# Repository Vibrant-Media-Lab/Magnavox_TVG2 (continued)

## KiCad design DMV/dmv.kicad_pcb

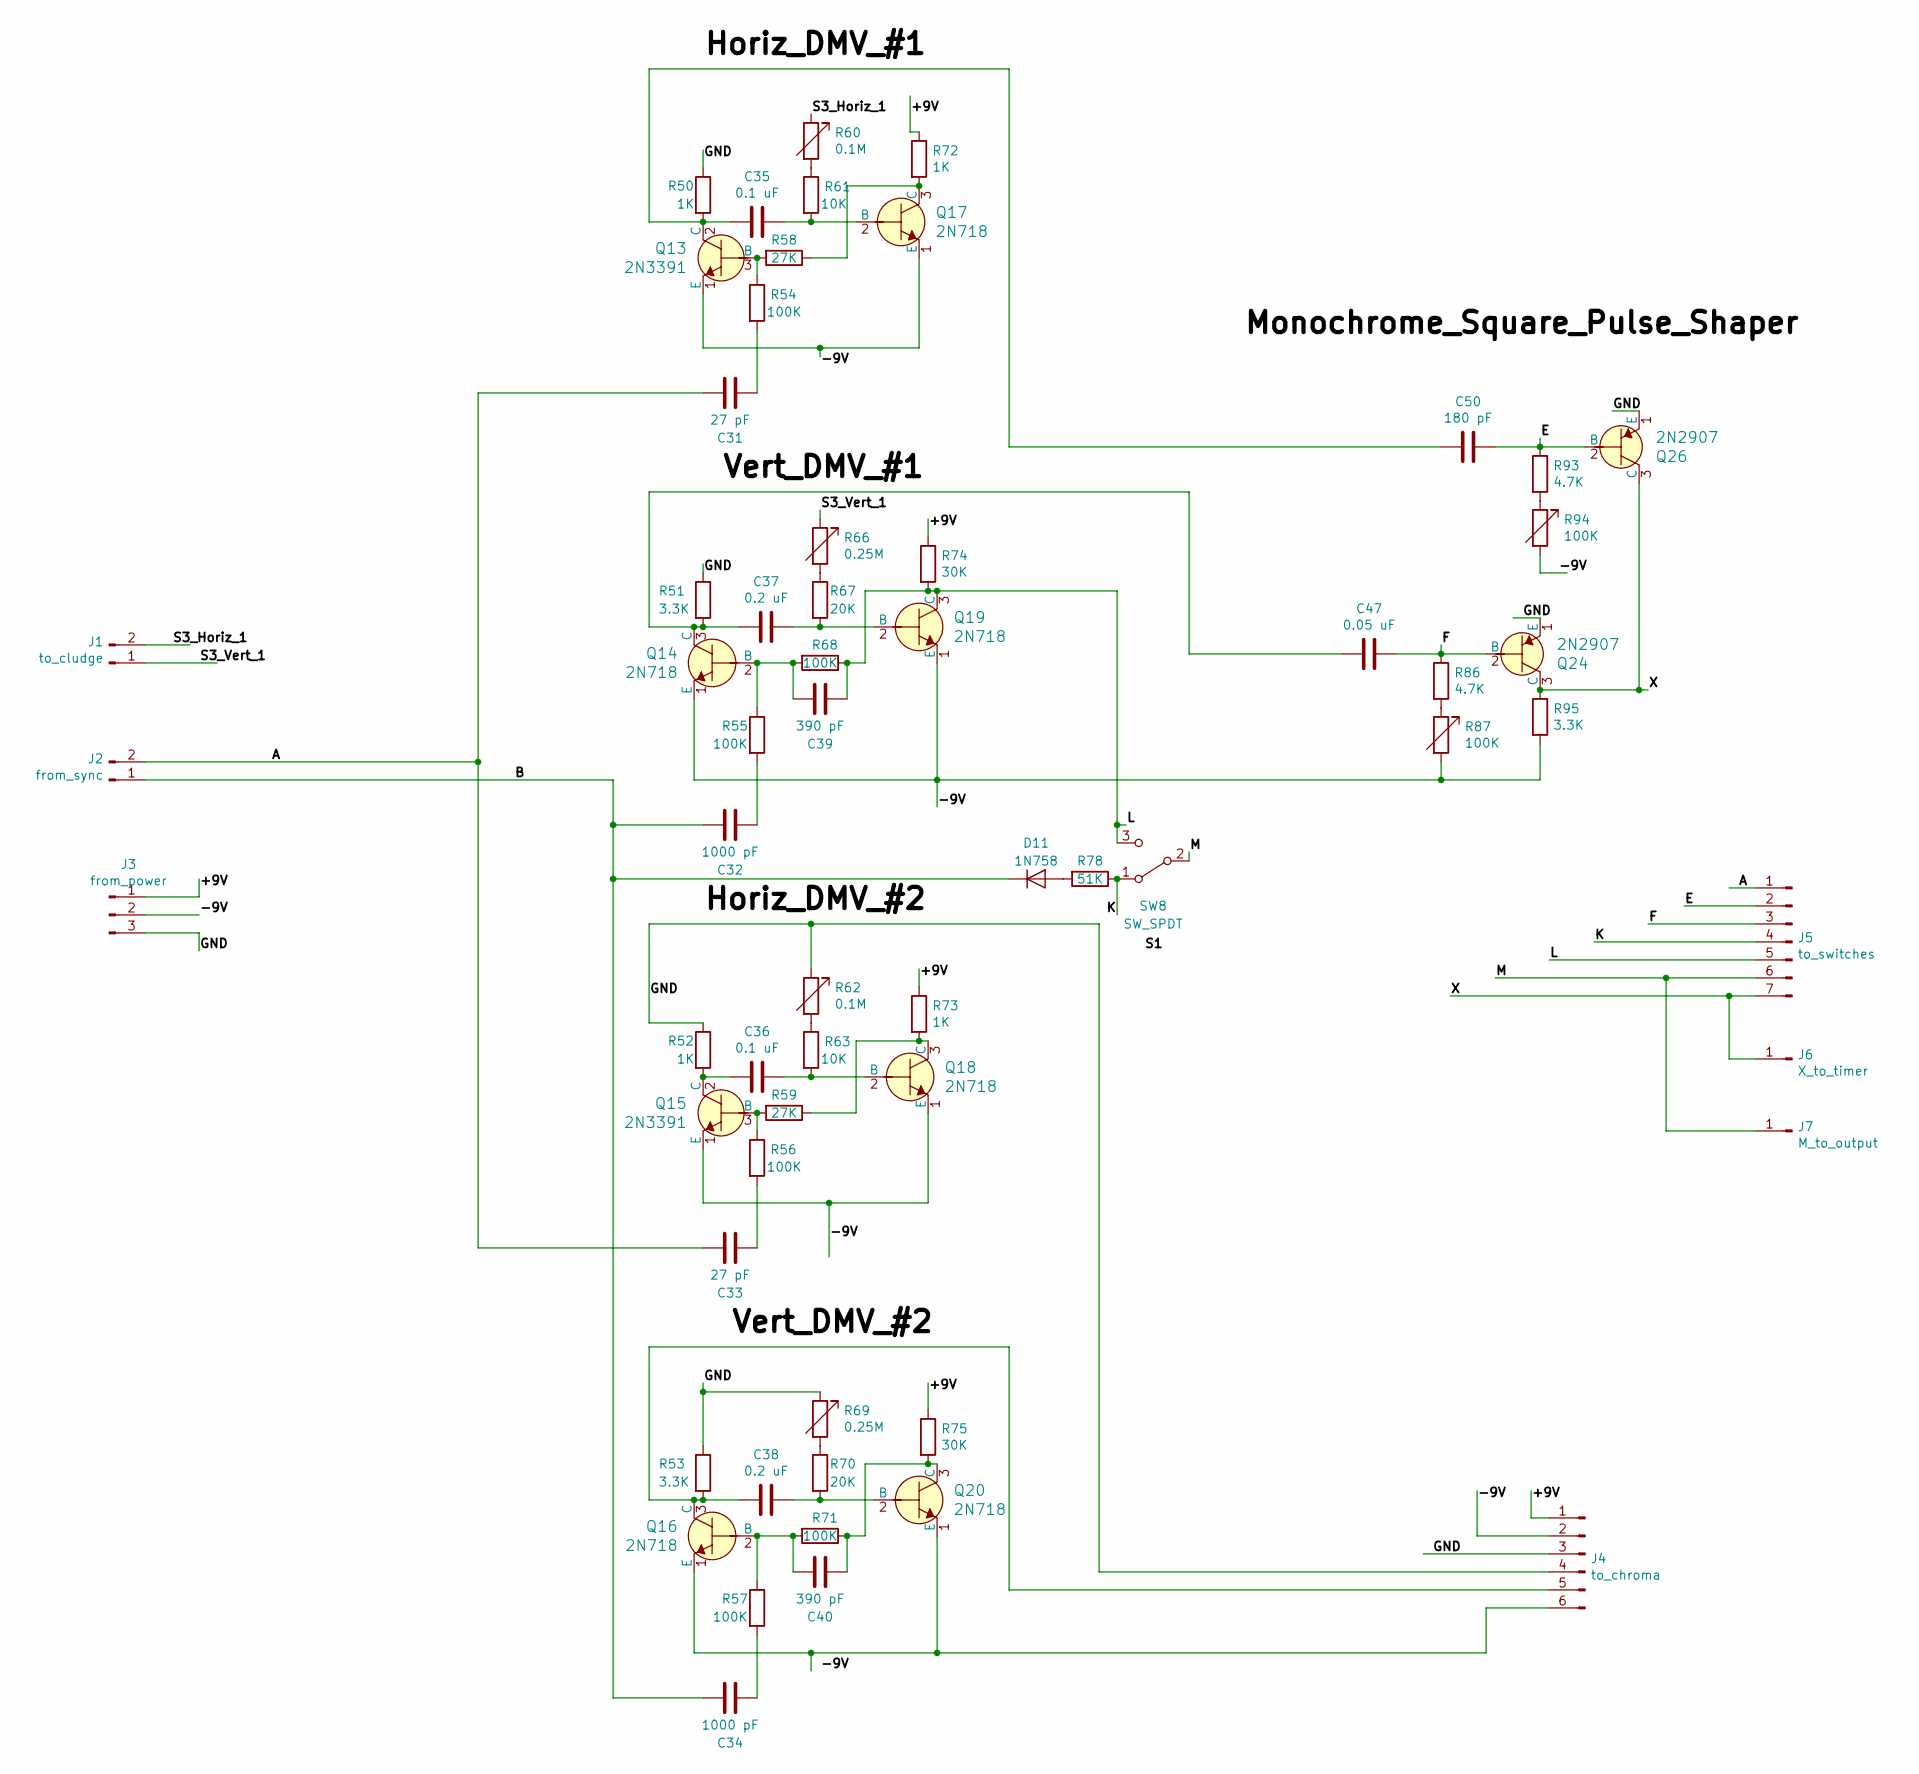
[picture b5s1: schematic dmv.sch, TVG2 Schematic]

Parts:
C31, C33: 27 pF; C_Disc_D4.7mm_W2.5mm_P5.00mm
C32, C34: 1000 pF; C_Disc_D4.7mm_W2.5mm_P5.00mm
C35, C36: 0.1 uF; C_Disc_D4.7mm_W2.5mm_P5.00mm
C37, C38: 0.2 uF; C_Disc_D4.7mm_W2.5mm_P5.00mm
C39, C40: 390 pF; C_Disc_D4.7mm_W2.5mm_P5.00mm
C47: 0.05 uF; C_Disc_D4.7mm_W2.5mm_P5.00mm
C50: 180 pF; C_Disc_D4.7mm_W2.5mm_P5.00mm
D11: 1N758; D_DO-41_SOD81_P10.16mm_Horizontal
J1: to_cludge; PinHeader_1x02_P2.54mm_Vertical
J2: from_sync; PinHeader_1x02_P2.54mm_Vertical
J3: from_power; PinHeader_1x03_P2.54mm_Vertical
J4: to_chroma; PinHeader_1x06_P2.54mm_Vertical
J5: to_switches; PinHeader_1x07_P2.54mm_Vertical
J6: X_to_timer; PinHeader_1x01_P2.54mm_Vertical
J7: M_to_output; PinHeader_1x01_P2.54mm_Vertical
Q13, Q15: 2N3391; TO-92-3; MPN 2N3904; Digi-Key_PN 2N3904CS-ND
Q14, Q16, Q17, Q18, Q19, Q20: 2N718; TO-92-3; MPN 2N5109; Digi-Key_PN 2N5109CS-ND
Q24, Q26: 2N2907; TO-92-3; MPN 2N2907A; Digi-Key_PN 2N2907ACS-ND
R50, R52, R72, R73: 1K; R_Axial_DIN0207_L6.3mm_D2.5mm_P7.62mm_Horizontal
R51, R53, R95: 3.3K; R_Axial_DIN0207_L6.3mm_D2.5mm_P7.62mm_Horizontal
R54, R55, R56, R57, R68, R71: 100K; R_Axial_DIN0207_L6.3mm_D2.5mm_P7.62mm_Horizontal
R58, R59: 27K; R_Axial_DIN0207_L6.3mm_D2.5mm_P7.62mm_Horizontal
R60, R62: 0.1M; Potentiometer_Bourns_3386F_Vertical
R61, R63: 10K; R_Axial_DIN0207_L6.3mm_D2.5mm_P7.62mm_Horizontal
R66, R69: 0.25M; Potentiometer_Bourns_3386F_Vertical
R67, R70: 20K; R_Axial_DIN0207_L6.3mm_D2.5mm_P7.62mm_Horizontal
R74, R75: 30K; R_Axial_DIN0207_L6.3mm_D2.5mm_P7.62mm_Horizontal
R78: 51K; R_Axial_DIN0207_L6.3mm_D2.5mm_P7.62mm_Horizontal
R86, R93: 4.7K; R_Axial_DIN0207_L6.3mm_D2.5mm_P7.62mm_Horizontal
R87, R94: 100K; Potentiometer_Bourns_3386F_Vertical
SW8: SW_SPDT; Toggle_Switch_100SP1T1B4M2QE

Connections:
/+9V: J3.1, J4.1, R72.1, R73.1, R74.1, R75.1
/-9V: J3.2, J4.2, Q14.1 (E), Q15.1 (E), Q18.1 (E), Q19.1 (E), R87.2, R94.2, R95.2
/A: C31.1, C33.1, J2.2, J5.1
/B: C32.2, C34.2, D11.1 (K), J2.1
/E: C50.1, J5.2, Q26.2 (B), R93.1
/F: C47.1, J5.3, Q24.2 (B), R86.1
/GND: J3.3, J4.3, J4.4, Q24.1 (E), Q26.1 (E), R50.1, R51.1, R52.1, R53.1, R62.1, R69.1
/K: J5.4, R78.1, SW8.1 (A)
/L: C39.1, J5.5, Q19.3 (C), R68.1, R74.2, SW8.3 (C)
/M: J5.6, J7.1, SW8.2 (B)
/S3_Horiz_1: J1.2, R60.1
/S3_Vert_1: J1.1, R66.1
/X: J5.7, J6.1, Q24.3 (C), Q26.3 (C), R95.1
unnamed: C31.2, R54.2
unnamed: C32.1, R55.2
unnamed: C33.2, R56.2
unnamed: C34.1, R57.2
unnamed: C35.1, C50.2, Q13.2 (C), R50.2
unnamed: C35.2, Q17.2 (B), R61.2
unnamed: C36.1, Q15.2 (C), R52.2
unnamed: C36.2, Q18.2 (B), R63.2
unnamed: C37.1, Q19.2 (B), R67.2
unnamed: C37.2, C47.2, Q14.3 (C), R51.2
unnamed: C38.1, Q20.2 (B), R70.2
unnamed: C38.2, J4.5, Q16.3 (C), R53.2
unnamed: C39.2, Q14.2 (B), R55.1, R68.2
unnamed: C40.1, Q20.3 (C), R71.1, R75.2
unnamed: C40.2, Q16.2 (B), R57.1, R71.2
unnamed: D11.2 (A), R78.2
unnamed: J4.6, Q16.1 (E), Q20.1 (E)
unnamed: Q13.1 (E), Q17.1 (E)
unnamed: Q13.3 (B), R54.1, R58.2
unnamed: Q15.3 (B), R56.1, R59.2
unnamed: Q17.3 (C), R58.1, R72.2
unnamed: Q18.3 (C), R59.1, R73.2
unnamed: R60.2, R61.1
unnamed: R62.2, R63.1
unnamed: R66.2, R67.1
unnamed: R69.2, R70.1
unnamed: R86.2, R87.1
unnamed: R93.2, R94.1

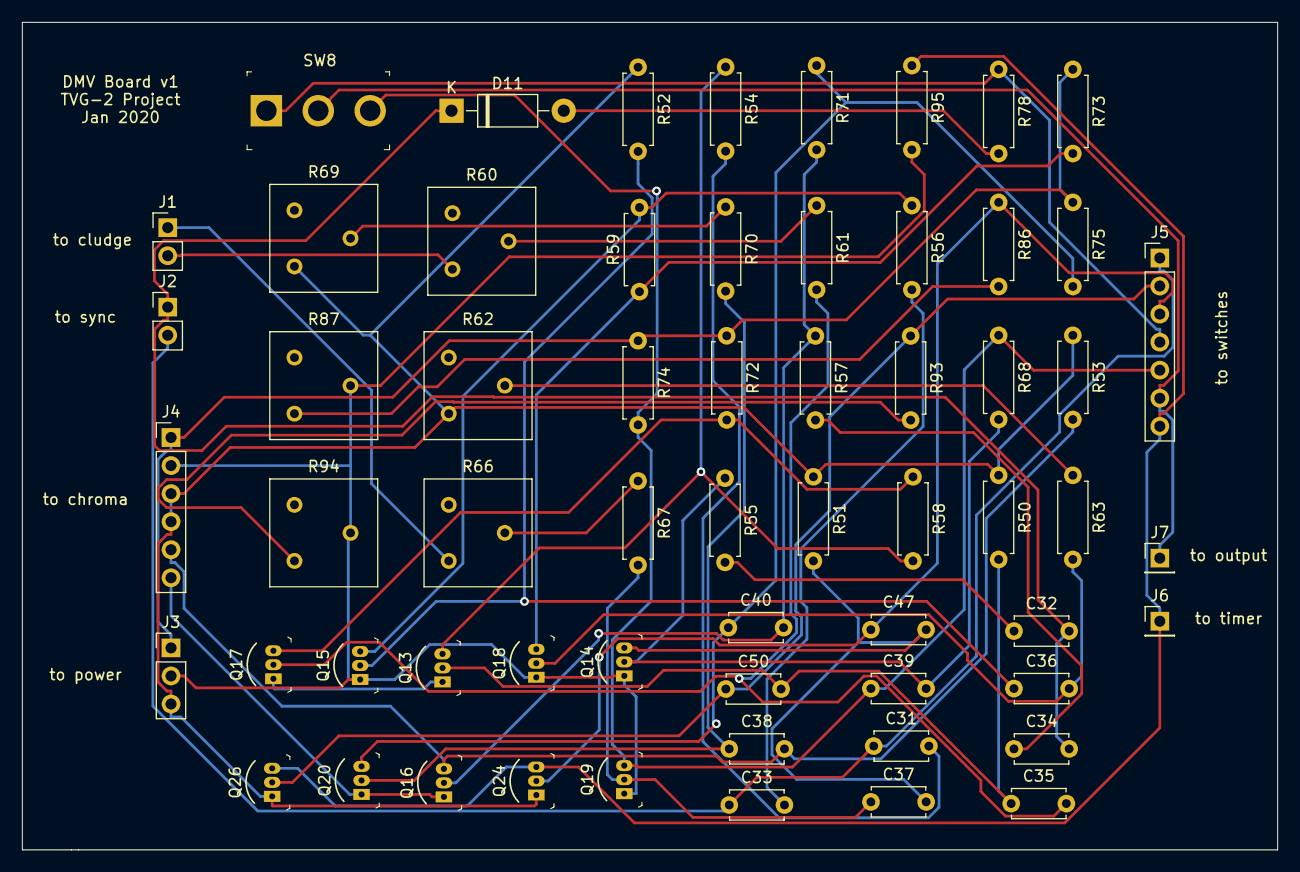
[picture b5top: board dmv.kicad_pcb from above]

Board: 2 copper layers, 113.7 x 74.9 mm, 61 parts (0 on the bottom side), 41 nets.

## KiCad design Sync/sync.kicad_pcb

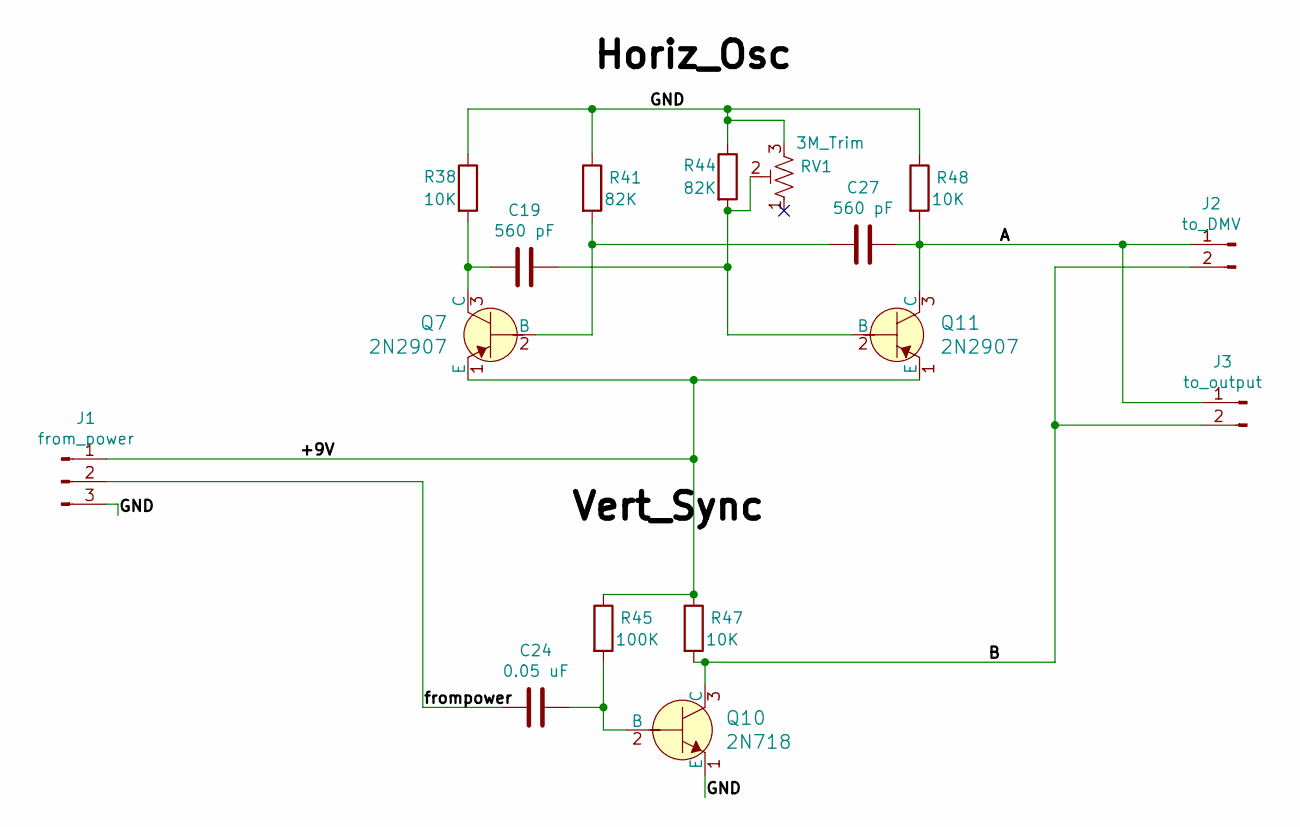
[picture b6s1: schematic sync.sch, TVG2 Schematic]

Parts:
C19, C27: 560 pF; C_Disc_D4.7mm_W2.5mm_P5.00mm
C24: 0.05 uF; C_Disc_D4.7mm_W2.5mm_P5.00mm
J1: from_power; PinHeader_1x03_P2.54mm_Vertical
J2: to_DMV; PinHeader_1x02_P2.54mm_Vertical
J3: to_output; PinHeader_1x02_P2.54mm_Vertical
Q7, Q11: 2N2907; TO-92-3; MPN 2N2907A; Digi-Key_PN 2N2907ACS-ND
Q10: 2N718; TO-92-3; MPN 2N5109; Digi-Key_PN 2N5109CS-ND
R38, R47, R48: 10K; R_Axial_DIN0207_L6.3mm_D2.5mm_P7.62mm_Horizontal
R41, R44: 82K; R_Axial_DIN0207_L6.3mm_D2.5mm_P7.62mm_Horizontal
R45: 100K; R_Axial_DIN0207_L6.3mm_D2.5mm_P7.62mm_Horizontal
RV1: 3M_Trim; Potentiometer_Bourns_3299Y_Vertical

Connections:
/+9V: J1.1, Q7.1 (E), Q11.1 (E), R45.1, R47.1
/A: C27.2, J2.1, J3.1, Q11.3 (C), R48.2
/B: J2.2, J3.2, Q10.3 (C), R47.2
/GND: J1.3, Q10.1 (E), R38.1, R41.1, R44.1, R48.1, RV1.3
/frompower: C24.1, J1.2
unnamed: C19.1, Q7.3 (C), R38.2
unnamed: C19.2, Q11.2 (B), R44.2, RV1.2
unnamed: C24.2, Q10.2 (B), R45.2
unnamed: C27.1, Q7.2 (B), R41.2

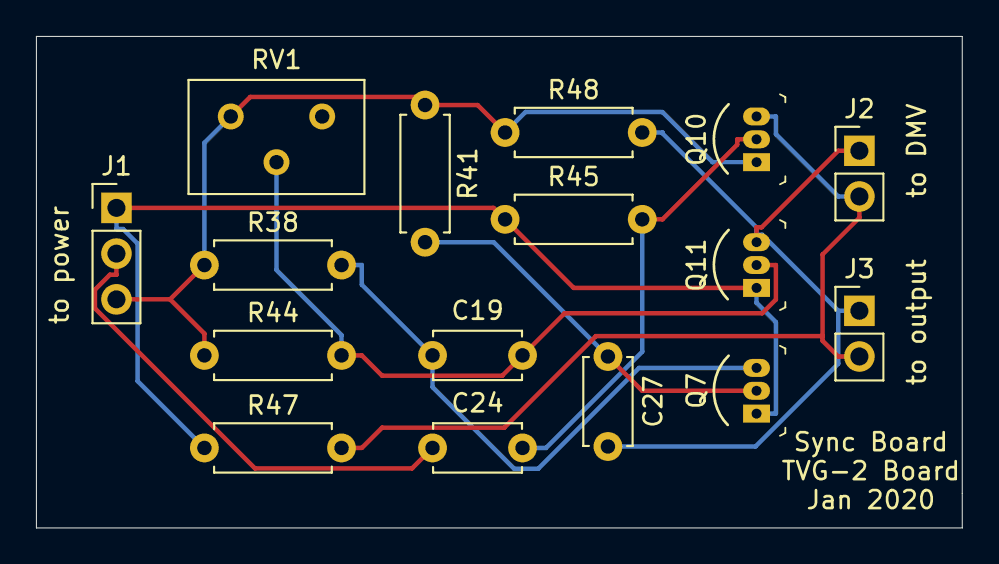
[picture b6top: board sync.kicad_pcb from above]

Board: 2 copper layers, 51.4 x 27.3 mm, 16 parts (0 on the bottom side), 9 nets.

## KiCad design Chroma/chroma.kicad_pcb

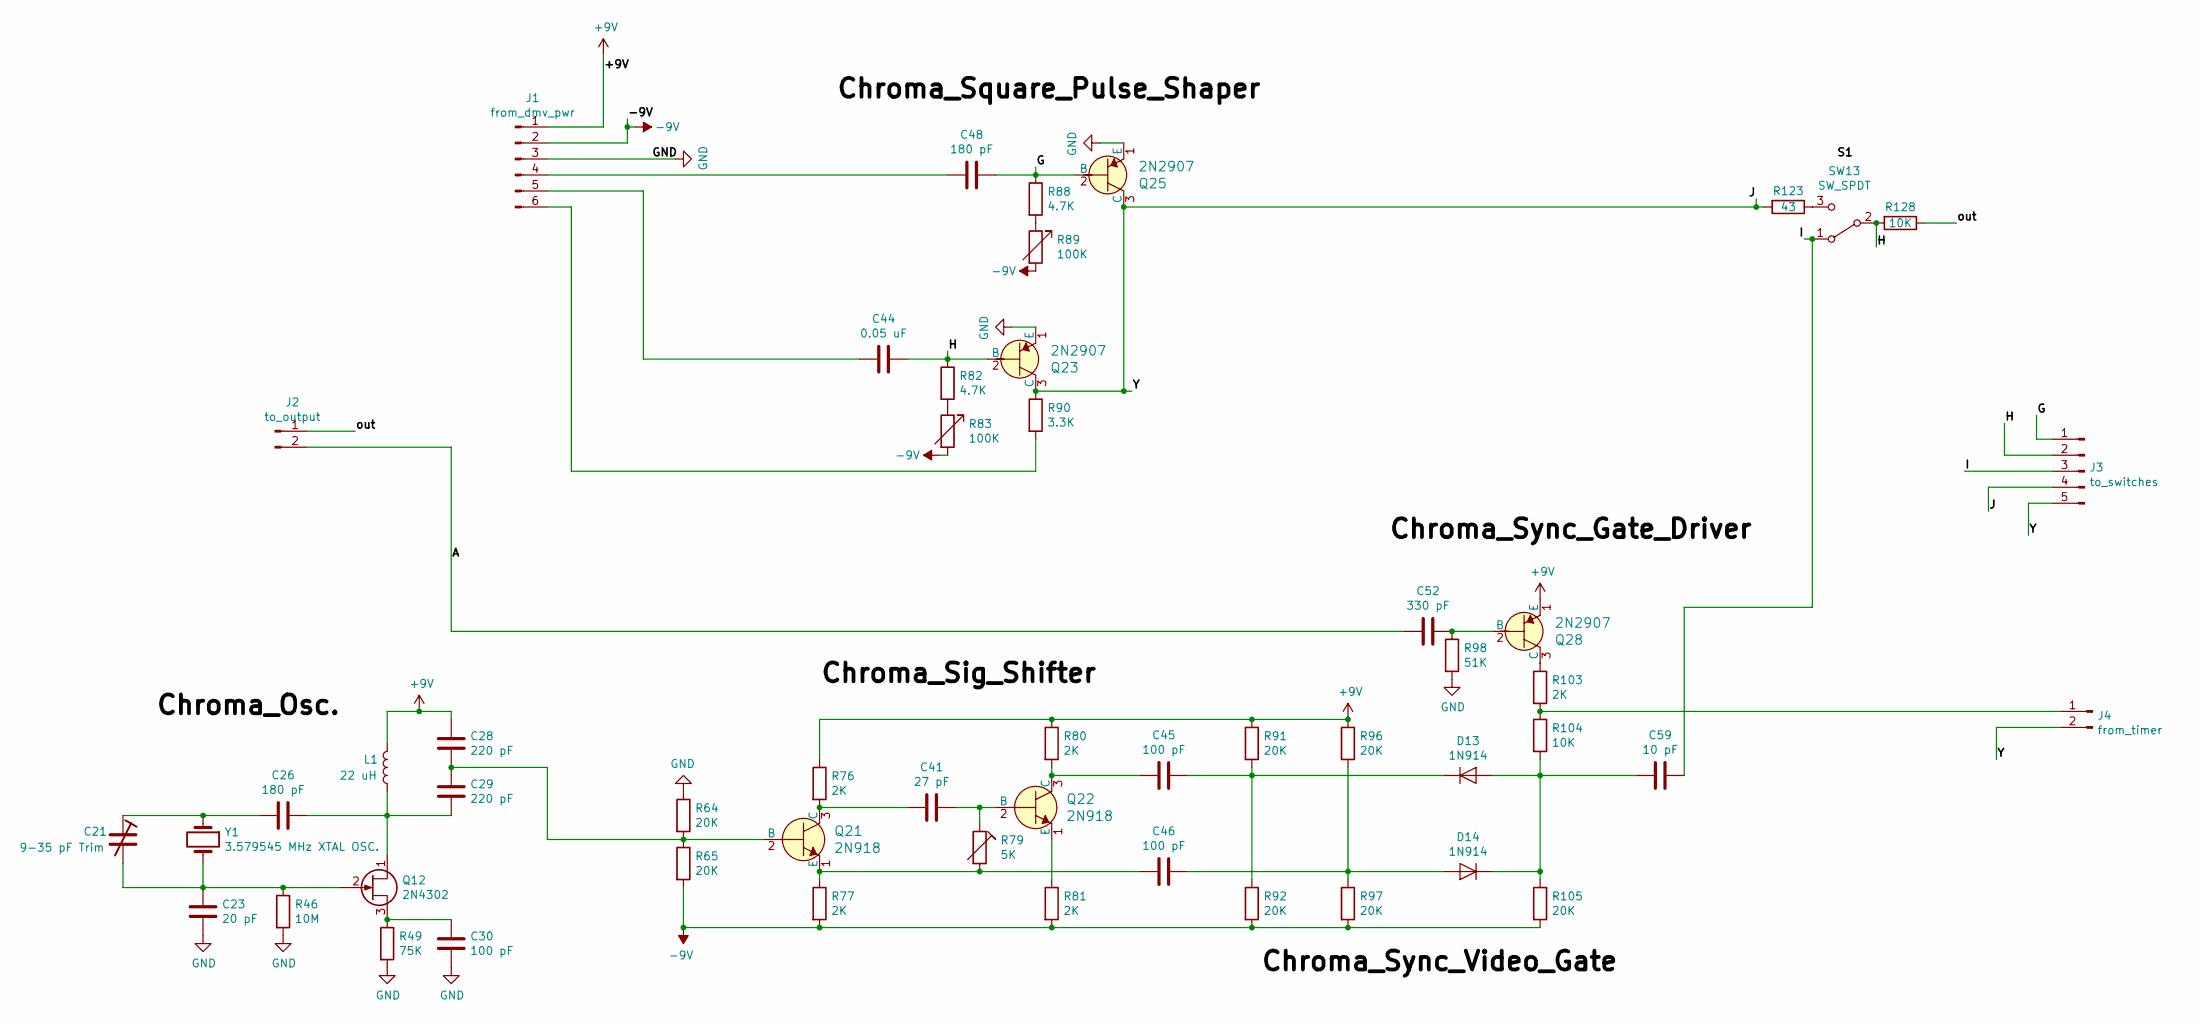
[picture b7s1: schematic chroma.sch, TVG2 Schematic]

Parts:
C21: 9-35 pF Trim; 9-35pF_Trim
C23: 20 pF; C_Disc_D4.7mm_W2.5mm_P5.00mm
C26, C48: 180 pF; C_Disc_D4.7mm_W2.5mm_P5.00mm
C28, C29: 220 pF; C_Disc_D4.7mm_W2.5mm_P5.00mm
C30, C45, C46: 100 pF; C_Disc_D4.7mm_W2.5mm_P5.00mm
C41: 27 pF; C_Disc_D4.7mm_W2.5mm_P5.00mm
C44: 0.05 uF; C_Disc_D4.7mm_W2.5mm_P5.00mm
C52: 330 pF; C_Disc_D4.7mm_W2.5mm_P5.00mm
C59: 10 pF; C_Disc_D4.7mm_W2.5mm_P5.00mm
D13, D14: 1N914; D_DO-35_SOD27_P7.62mm_Horizontal
J1: from_dmv_pwr; PinHeader_1x06_P2.54mm_Vertical
J2: to_output; PinHeader_1x02_P2.54mm_Vertical
J3: to_switches; PinHeader_1x05_P2.54mm_Vertical
J4: from_timer; PinHeader_1x02_P2.54mm_Vertical
L1: 22 uH; R_Axial_DIN0207_L6.3mm_D2.5mm_P7.62mm_Horizontal
Q12: 2N4302; TO-92-3
Q21, Q22: 2N918; TO-92-3; MPN 2N5109; Digi-Key_PN 2N5109CS-ND
Q23, Q25, Q28: 2N2907; TO-92-3; MPN 2N2907A; Digi-Key_PN 2N2907ACS-ND
R46: 10M; R_Axial_DIN0207_L6.3mm_D2.5mm_P7.62mm_Horizontal
R49: 75K; R_Axial_DIN0207_L6.3mm_D2.5mm_P7.62mm_Horizontal
R64, R65, R91, R92, R96, R97, R105: 20K; R_Axial_DIN0207_L6.3mm_D2.5mm_P7.62mm_Horizontal
R76, R77, R80, R81, R103: 2K; R_Axial_DIN0207_L6.3mm_D2.5mm_P7.62mm_Horizontal
R79: 5K; Potentiometer_Bourns_3386F_Vertical
R82, R88: 4.7K; R_Axial_DIN0207_L6.3mm_D2.5mm_P7.62mm_Horizontal
R83, R89: 100K; Potentiometer_Bourns_3386F_Vertical
R90: 3.3K; R_Axial_DIN0207_L6.3mm_D2.5mm_P7.62mm_Horizontal
R98: 51K; R_Axial_DIN0207_L6.3mm_D2.5mm_P7.62mm_Horizontal
R104, R128: 10K; R_Axial_DIN0207_L6.3mm_D2.5mm_P7.62mm_Horizontal
R123: 43; R_Axial_DIN0207_L6.3mm_D2.5mm_P7.62mm_Horizontal
SW13: SW_SPDT; Toggle_Switch_100SP1T1B4M2QE
Y1: 3.579545 MHz XTAL OSC.; R_Axial_DIN0516_L15.5mm_D5.0mm_P5.08mm_Vertical

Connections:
+9V: C28.2, J1.1, L1.2, Q28.1 (E), R76.1, R80.1, R91.1, R96.1
-9V: J1.2, R65.2, R77.2, R81.2, R83.2, R89.2, R92.2, R97.2, R105.2
/A: C52.1, J2.2
/G: C48.1, J3.1, Q25.2 (B), R88.1
/H: C44.1, J3.2, Q23.2 (B), R82.1, R128.2, SW13.2 (B)
/I: C59.2, J3.3, SW13.1 (A)
/J: J3.4, J3.5, J4.2, Q23.3 (C), Q25.3 (C), R90.1, R123.2
/out: J2.1, R128.1
GND: C23.1, C30.1, J1.3, Q23.1 (E), Q25.1 (E), R46.2, R49.2, R64.1, R98.2
unnamed: C21.1, C26.2, Y1.1
unnamed: C21.2, C23.2, Q12.2 (G), R46.1, Y1.2
unnamed: C26.1, C29.1, L1.1, Q12.1 (D)
unnamed: C28.1, C29.2, Q21.2 (B), R64.2, R65.1
unnamed: C30.2, Q12.3 (S), R49.1
unnamed: C41.1, Q22.2 (B), R79.1
unnamed: C41.2, Q21.3 (C), R76.2
unnamed: C44.2, J1.5
unnamed: C45.1, Q22.3 (C), R80.2
unnamed: C45.2, D13.1 (K), R91.2, R92.1
unnamed: C46.1, Q21.1 (E), R77.1, R79.2
unnamed: C46.2, D14.2 (A), R96.2, R97.1
unnamed: C48.2, J1.4
unnamed: C52.2, Q28.2 (B), R98.1
unnamed: C59.1, D13.2 (A), D14.1 (K), R104.2, R105.1
unnamed: J1.6, R90.2
unnamed: J4.1, R103.2, R104.1
unnamed: Q22.1 (E), R81.1
unnamed: Q28.3 (C), R103.1
unnamed: R82.2, R83.1
unnamed: R88.2, R89.1
unnamed: R123.1, SW13.3 (C)

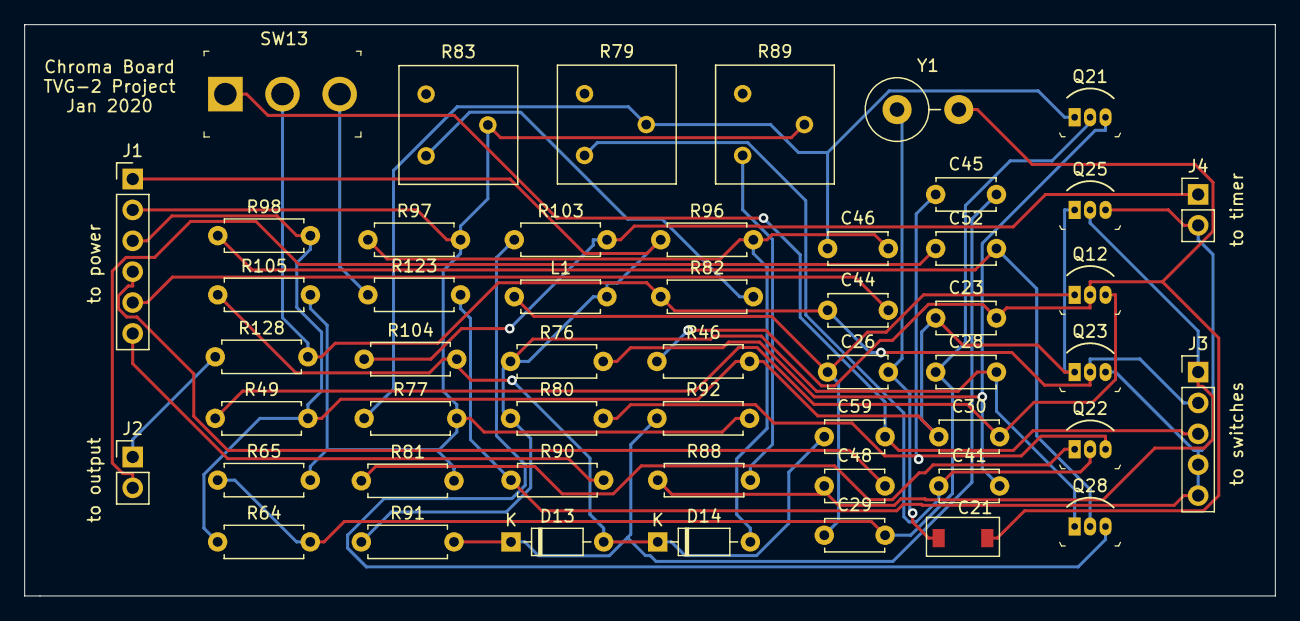
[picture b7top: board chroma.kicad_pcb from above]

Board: 2 copper layers, 102.9 x 47.0 mm, 52 parts (0 on the bottom side), 31 nets.

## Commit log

2023-08-04 Finished PSU and Sync Generation
2023-08-06 Finished DMV, Added original and supplimentary documents
2023-08-06 added legacy release 1.0 files
2023-08-06 Added VDO Mono and Choma
2023-08-07 Finished VDO for Chroma and Mono
2023-08-07 Corrected resistor value
2023-08-08 Coincidence Gate, SCR and Timer setup
2023-08-08 Coincidence Gate, SCR and Timer update
2023-08-09 SCR revision and SPICE model
2023-08-12 Timer circuit completed
2023-08-14 discovered Ralph's biography, complete understanding of circuit obtained. Beginning complete SPICE modeling
2023-08-21 modified spice files
2023-08-21 modified spice
2023-08-24 DMV changes:
2023-08-25 VDO board modifications, TVP5147 Composite to Component considered.
2023-08-25 added Composite handbook
2023-08-25 Bring up to date with 2.0dev
2024-01-30 start 2.0 rev2 schematic
2024-01-30 DMV complete, fully socketed
2024-01-31 DMV layout complete
2024-01-31 deteled SVG
2024-02-01 changed DMV layout, routing started
2024-02-01 finished DMV board
2024-02-01 corrected silkscreen
